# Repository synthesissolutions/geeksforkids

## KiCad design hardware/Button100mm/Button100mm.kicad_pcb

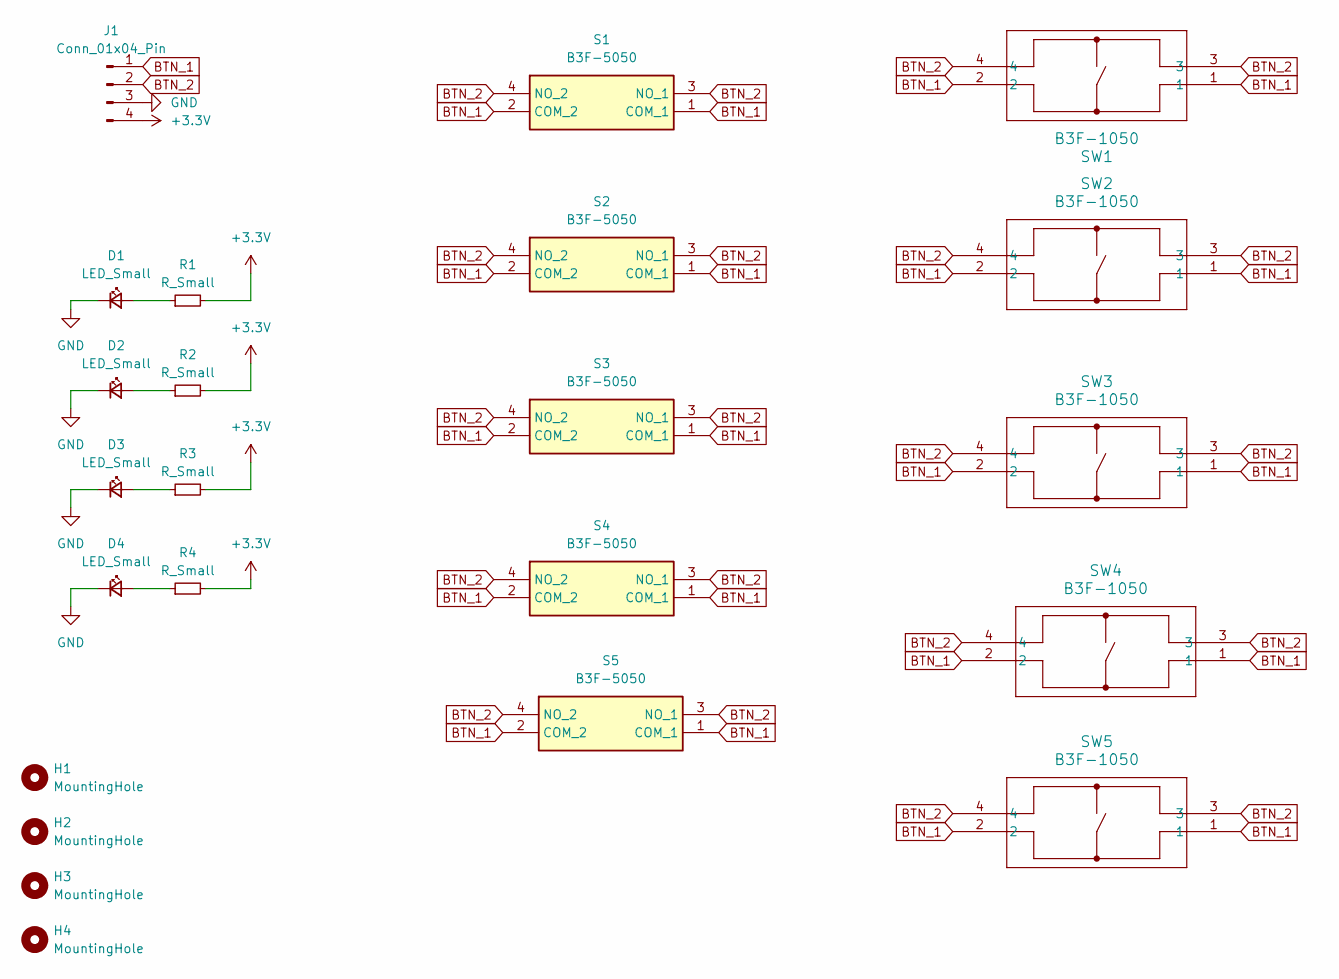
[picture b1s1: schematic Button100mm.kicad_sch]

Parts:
D1, D2, D3, D4: LED_Small; LED_0805_2012Metric
H1, H2, H3, H4: MountingHole; MountingHole_2.7mm_M2.5
J1: Conn_01x04_Pin; JST_XH_B4B-XH-A_1x04_P2.50mm_Vertical
R1, R2, R3, R4: R_Small; R_0805_2012Metric
S1, S2, S3, S4, S5: B3F-5050; B3F-4055; Mouser Part Number 653-B3F-5050
SW1, SW2, SW3, SW4, SW5: B3F-1050; SW_B3F-1050_OMR

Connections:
+3.3V: J1.4, R1.2, R2.2, R3.2, R4.2
BTN_1: J1.1, S1.1 (COM_1), S1.2 (COM_2), S2.1 (COM_1), S2.2 (COM_2), S3.1 (COM_1), S3.2 (COM_2), S4.1 (COM_1), S4.2 (COM_2), S5.1 (COM_1), S5.2 (COM_2), SW1.1, SW1.2, SW2.1, SW2.2, SW3.1, SW3.2, SW4.1, SW4.2, SW5.1, SW5.2
BTN_2: J1.2, S1.3 (NO_1), S1.4 (NO_2), S2.3 (NO_1), S2.4 (NO_2), S3.3 (NO_1), S3.4 (NO_2), S4.3 (NO_1), S4.4 (NO_2), S5.3 (NO_1), S5.4 (NO_2), SW1.3, SW1.4, SW2.3, SW2.4, SW3.3, SW3.4, SW4.3, SW4.4, SW5.3, SW5.4
GND: D1.1 (K), D2.1 (K), D3.1 (K), D4.1 (K), J1.3
unnamed: D1.2 (A), R1.1
unnamed: D2.2 (A), R2.1
unnamed: D3.2 (A), R3.1
unnamed: D4.2 (A), R4.1

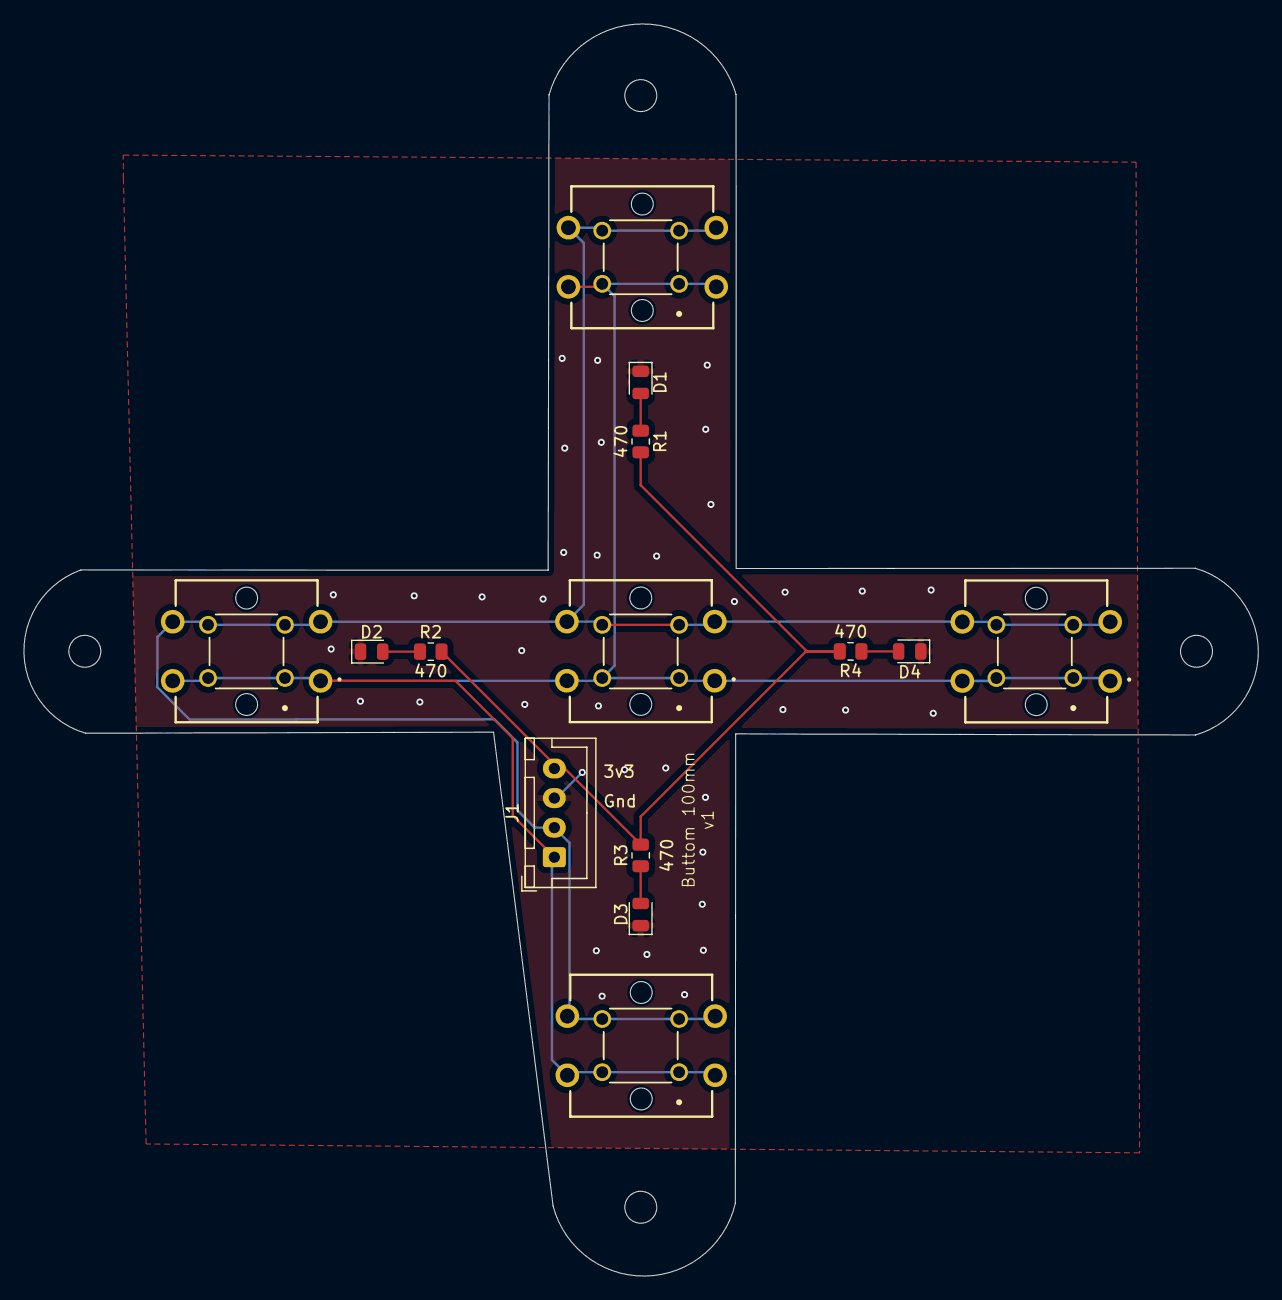
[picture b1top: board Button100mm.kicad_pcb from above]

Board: 2 copper layers, 104.4 x 105.9 mm, 23 parts (0 on the bottom side), 8 nets.

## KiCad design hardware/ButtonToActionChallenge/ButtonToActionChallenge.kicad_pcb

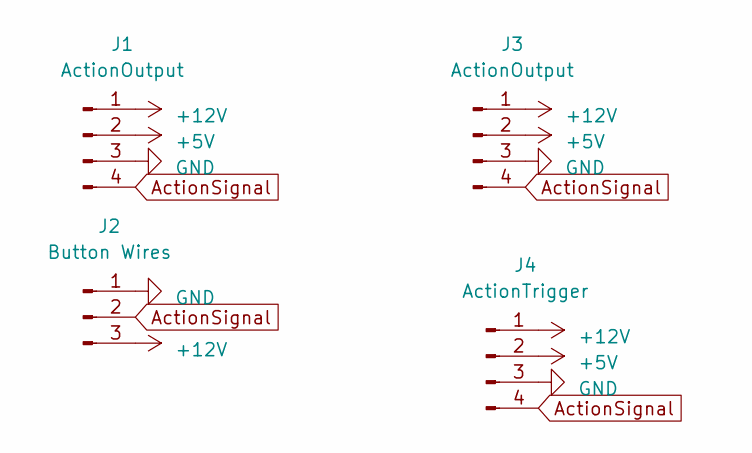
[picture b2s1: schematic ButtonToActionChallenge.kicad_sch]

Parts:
J1: ActionOutput; JST_PH_B4B-PH-K_1x04_P2.00mm_Vertical
J2: Button Wires; JST_XH_B3B-XH-A_1x03_P2.50mm_Vertical
J3: ActionOutput; JST_XH_B4B-XH-A_1x04_P2.50mm_Vertical
J4: ActionTrigger; JST_PH_B4B-PH-K_1x04_P2.00mm_Vertical

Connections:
+5V: J1.2, J3.2, J4.2
+12V: J1.1, J2.3, J3.1, J4.1
ActionSignal: J1.4, J2.2, J3.4, J4.4
GND: J1.3, J2.1, J3.3, J4.3

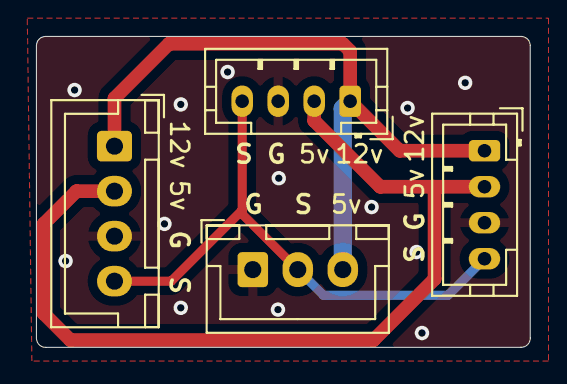
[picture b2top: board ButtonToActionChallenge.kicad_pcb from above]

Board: 2 copper layers, 27.4 x 17.3 mm, 4 parts (0 on the bottom side), 4 nets.

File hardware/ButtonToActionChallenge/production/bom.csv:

Designator,Footprint,Quantity,Value,LCSC Part #
J1,JST_PH_B4B-PH-K_1x04_P2.00mm_Vertical,1,ActionOutput,
J2,JST_XH_B3B-XH-A_1x03_P2.50mm_Vertical,1,Button Wires,
J3,JST_XH_B4B-XH-A_1x04_P2.50mm_Vertical,1,ActionOutput,
J4,JST_PH_B4B-PH-K_1x04_P2.00mm_Vertical,1,ActionTrigger,

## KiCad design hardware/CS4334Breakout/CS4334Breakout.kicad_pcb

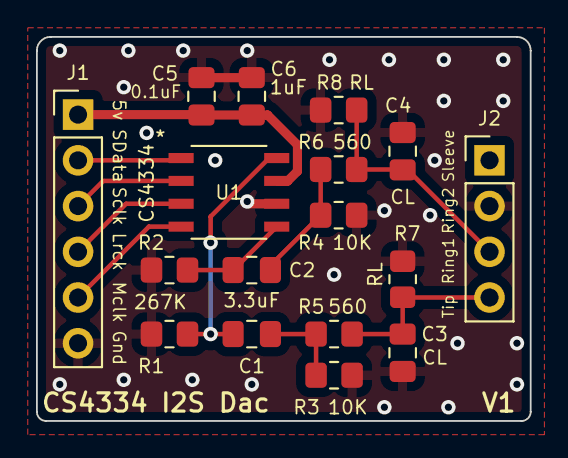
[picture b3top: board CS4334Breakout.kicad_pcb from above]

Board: 2 copper layers, 27.4 x 21.3 mm, 17 parts (0 on the bottom side), 12 nets.

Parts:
C1, C2: 3.3uF; C_0805_2012Metric_Pad1.18x1.45mm_HandSolder
C3, C4: CL; C_0805_2012Metric_Pad1.18x1.45mm_HandSolder
C5: 0.1uF; C_0805_2012Metric_Pad1.18x1.45mm_HandSolder
C6: 1uF; C_0805_2012Metric_Pad1.18x1.45mm_HandSolder
J1: I2S and Power Header; PinHeader_1x06_P2.54mm_Vertical
J2: HeadphoneOutput; PinHeader_1x04_P2.54mm_Vertical
R1, R2: 267K; R_0805_2012Metric_Pad1.20x1.40mm_HandSolder
R3, R4: 10K; R_0805_2012Metric_Pad1.20x1.40mm_HandSolder
R5, R6: 560; R_0805_2012Metric_Pad1.20x1.40mm_HandSolder
R7, R8: RL; R_0805_2012Metric_Pad1.20x1.40mm_HandSolder
U1: CS4334; CS4334-KSZR

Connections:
+5V: C5.1, C6.1, J1.1, U1.7 (VA)
AOUTL: C1.1, R1.1, U1.8 (AOUTL)
AOUTR: C2.1, R2.1, U1.5 (AOUTR)
GND: C3.2, C4.2, C5.2, C6.2, J1.6, J2.2, R1.2, R2.2, R3.2, R4.2, R7.2, R8.2, U1.6 (AGND)
LEFTOUT: C3.1, J2.4, R5.2, R7.1
LRCK: J1.4, U1.3 (LRCK)
MCLK: J1.5, U1.4 (MCLK)
unnamed: C1.2, R3.1, R5.1
unnamed: C2.2, R4.1, R6.1
RIGHTOUT: C4.1, J2.3, R6.2, R8.1
SCLK: J1.3, U1.2 (DEM/SCLK)
SDATA: J1.2, U1.1 (SDATA)

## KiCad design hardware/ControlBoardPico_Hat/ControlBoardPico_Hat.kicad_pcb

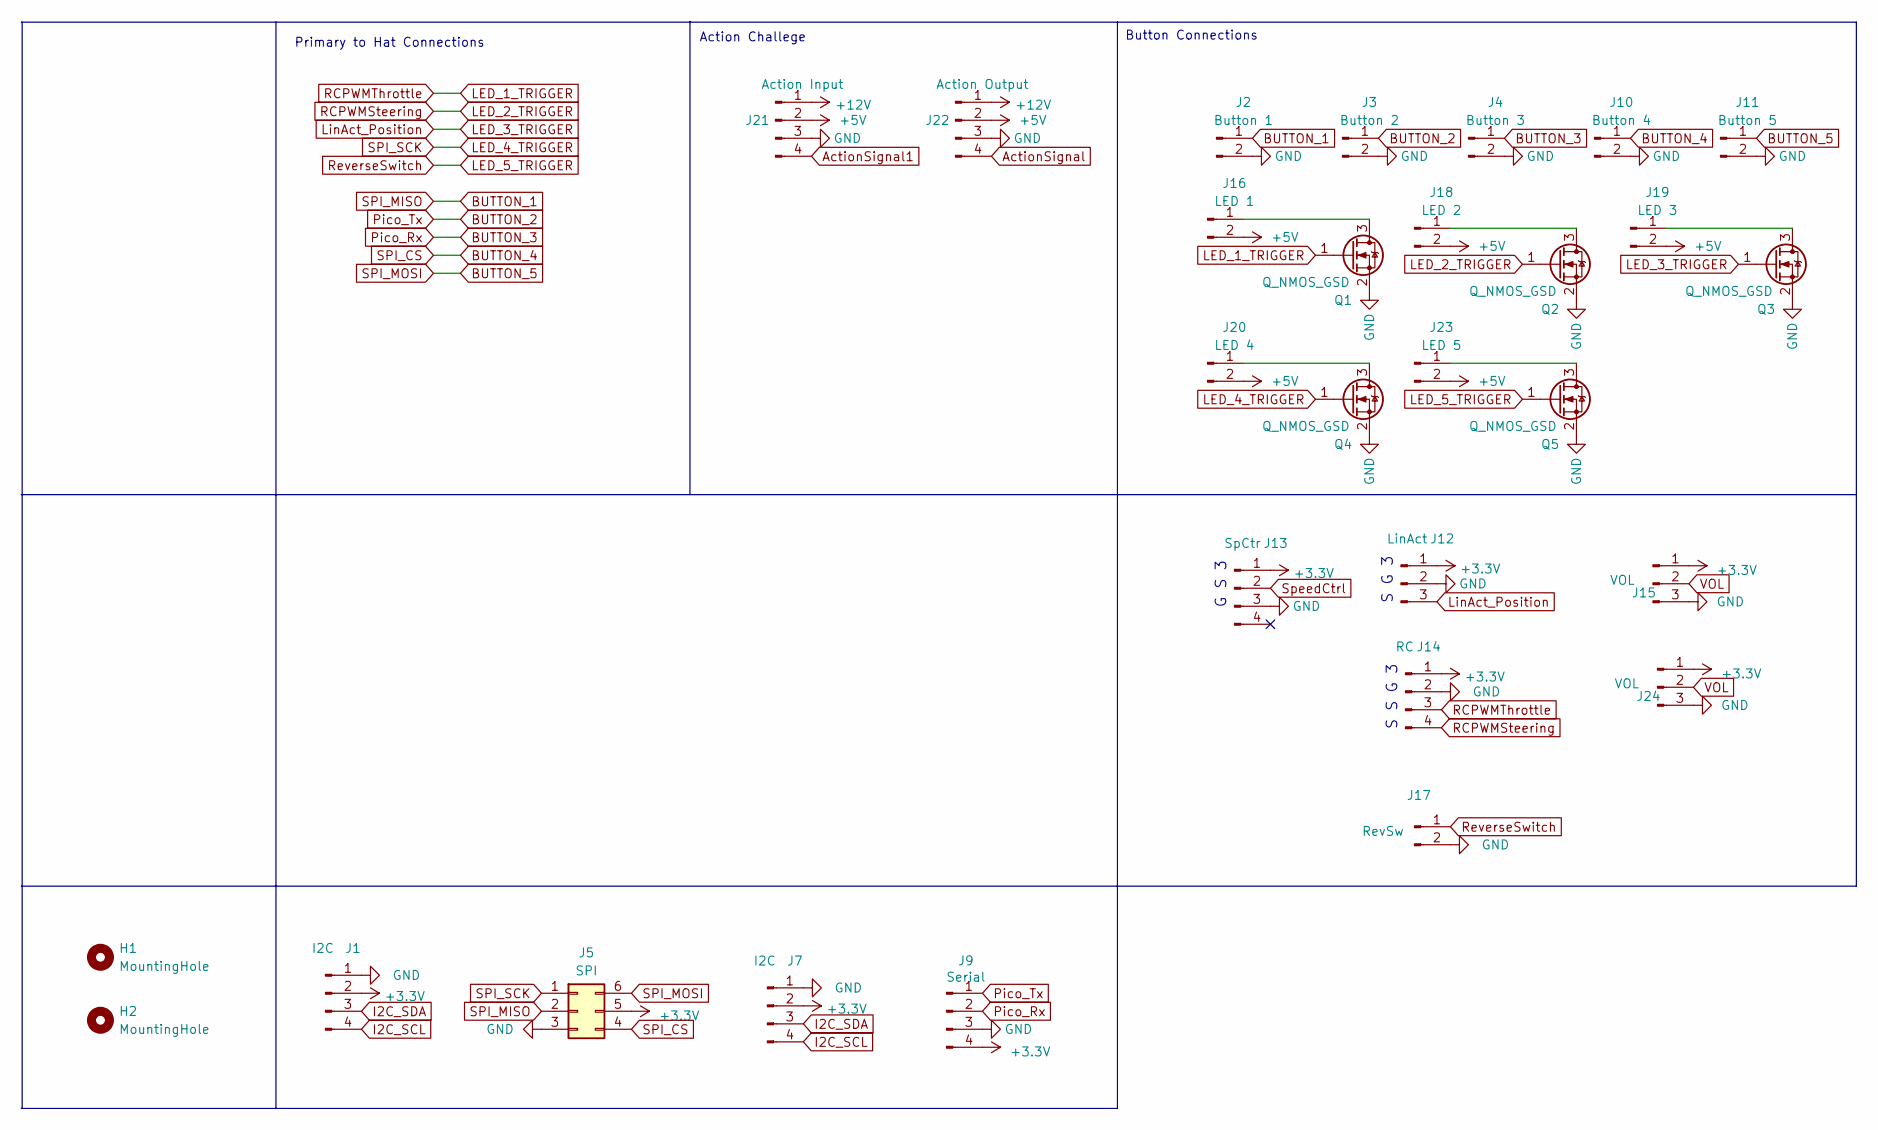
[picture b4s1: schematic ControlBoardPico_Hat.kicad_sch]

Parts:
H1, H2: MountingHole; MountingHole_2.7mm_M2.5
J1: I2C; JST_SH_BM04B-SRSS-TB_1x04-1MP_P1.00mm_Vertical
J2: Button 1; JST_XH_B2B-XH-A_1x02_P2.50mm_Vertical
J3: Button 2; JST_XH_B2B-XH-A_1x02_P2.50mm_Vertical
J4: Button 3; JST_XH_B2B-XH-A_1x02_P2.50mm_Vertical
J5: SPI; PinHeader_2x03_P2.54mm_Vertical
J7: I2C; PinHeader_1x04_P2.54mm_Vertical
J9: Serial; PinHeader_1x04_P2.54mm_Vertical
J10: Button 4; JST_XH_B2B-XH-A_1x02_P2.50mm_Vertical
J11: Button 5; JST_XH_B2B-XH-A_1x02_P2.50mm_Vertical
J12: LinAct; PinSocket_1x03_P2.54mm_Vertical
J13: SpCtr; PinSocket_1x04_P2.00mm_Vertical
J14: RC; PinSocket_1x04_P2.54mm_Vertical
J15: VOL; PinSocket_1x03_P2.00mm_Vertical
J16: LED 1; JST_XH_B2B-XH-A_1x02_P2.50mm_Vertical
J17: RevSw; PinSocket_1x02_P2.54mm_Vertical
J18: LED 2; JST_XH_B2B-XH-A_1x02_P2.50mm_Vertical
J19: LED 3; JST_XH_B2B-XH-A_1x02_P2.50mm_Vertical
J20: LED 4; JST_XH_B2B-XH-A_1x02_P2.50mm_Vertical
J21: Action Input; PinSocket_1x04_P2.54mm_Vertical
J22: Action Output; PinSocket_1x04_P2.54mm_Vertical
J23: LED 5; JST_XH_B2B-XH-A_1x02_P2.50mm_Vertical
J24: VOL; JST_XH_B3B-XH-A_1x03_P2.50mm_Vertical
Q1, Q2, Q3, Q4, Q5: Q_NMOS_GSD; SOT-23

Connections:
+3.3V: J1.2, J5.5, J7.2, J9.4, J12.1, J13.1, J14.1, J15.1, J24.1
+5V: J16.2, J18.2, J19.2, J20.2, J21.2, J22.2, J23.2
+12V: J21.1, J22.1
ActionSignal: J22.4
ActionSignal1: J21.4
BUTTON_1: J2.1, J5.2
BUTTON_2: J3.1, J9.1
BUTTON_3: J4.1, J9.2
BUTTON_4: J5.4, J10.1
BUTTON_5: J5.6, J11.1
GND: J1.1, J2.2, J3.2, J4.2, J5.3, J7.1, J9.3, J10.2, J11.2, J12.2, J13.3, J14.2, J15.3, J17.2, J21.3, J22.3, J24.3, Q1.2 (S), Q2.2 (S), Q3.2 (S), Q4.2 (S), Q5.2 (S)
I2C_SCL: J1.4, J7.4
I2C_SDA: J1.3, J7.3
LED_1_TRIGGER: J14.3, Q1.1 (G)
LED_2_TRIGGER: J14.4, Q2.1 (G)
LED_3_TRIGGER: J12.3, Q3.1 (G)
LED_4_TRIGGER: J5.1, Q4.1 (G)
LED_5_TRIGGER: J17.1, Q5.1 (G)
unnamed: J16.1, Q1.3 (D)
unnamed: J18.1, Q2.3 (D)
unnamed: J19.1, Q3.3 (D)
unnamed: J20.1, Q4.3 (D)
unnamed: J23.1, Q5.3 (D)
SpeedCtrl: J13.2
VOL: J15.2, J24.2

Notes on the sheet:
G S 3
S S G 3
Button Connections
Primary to Hat Connections
Action Challege
S G 3

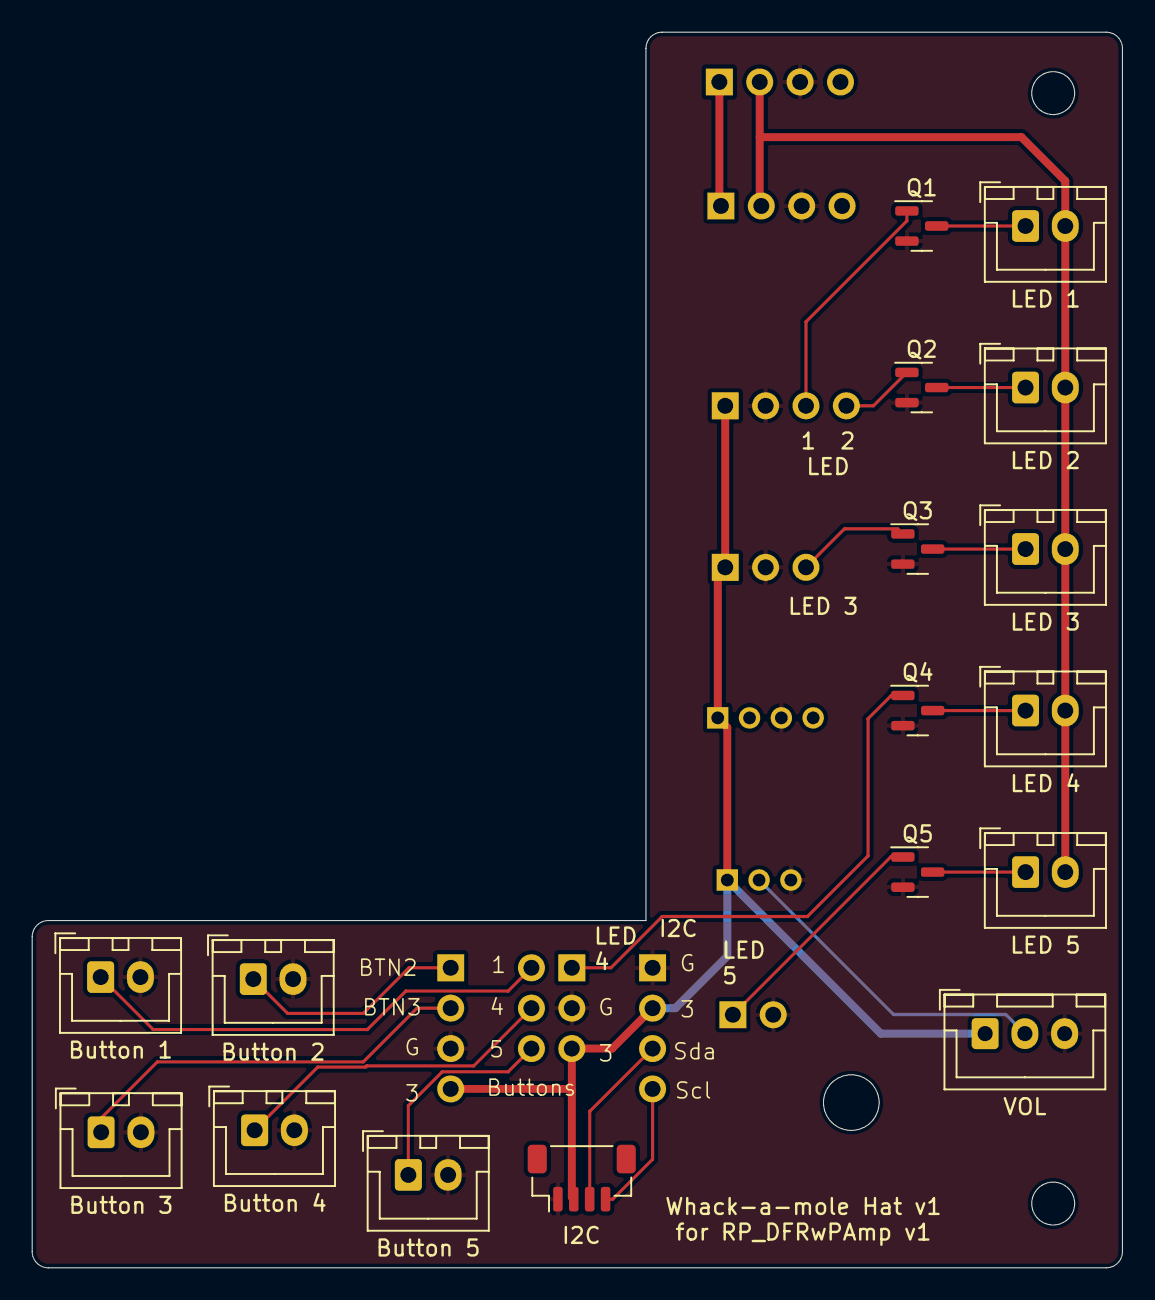
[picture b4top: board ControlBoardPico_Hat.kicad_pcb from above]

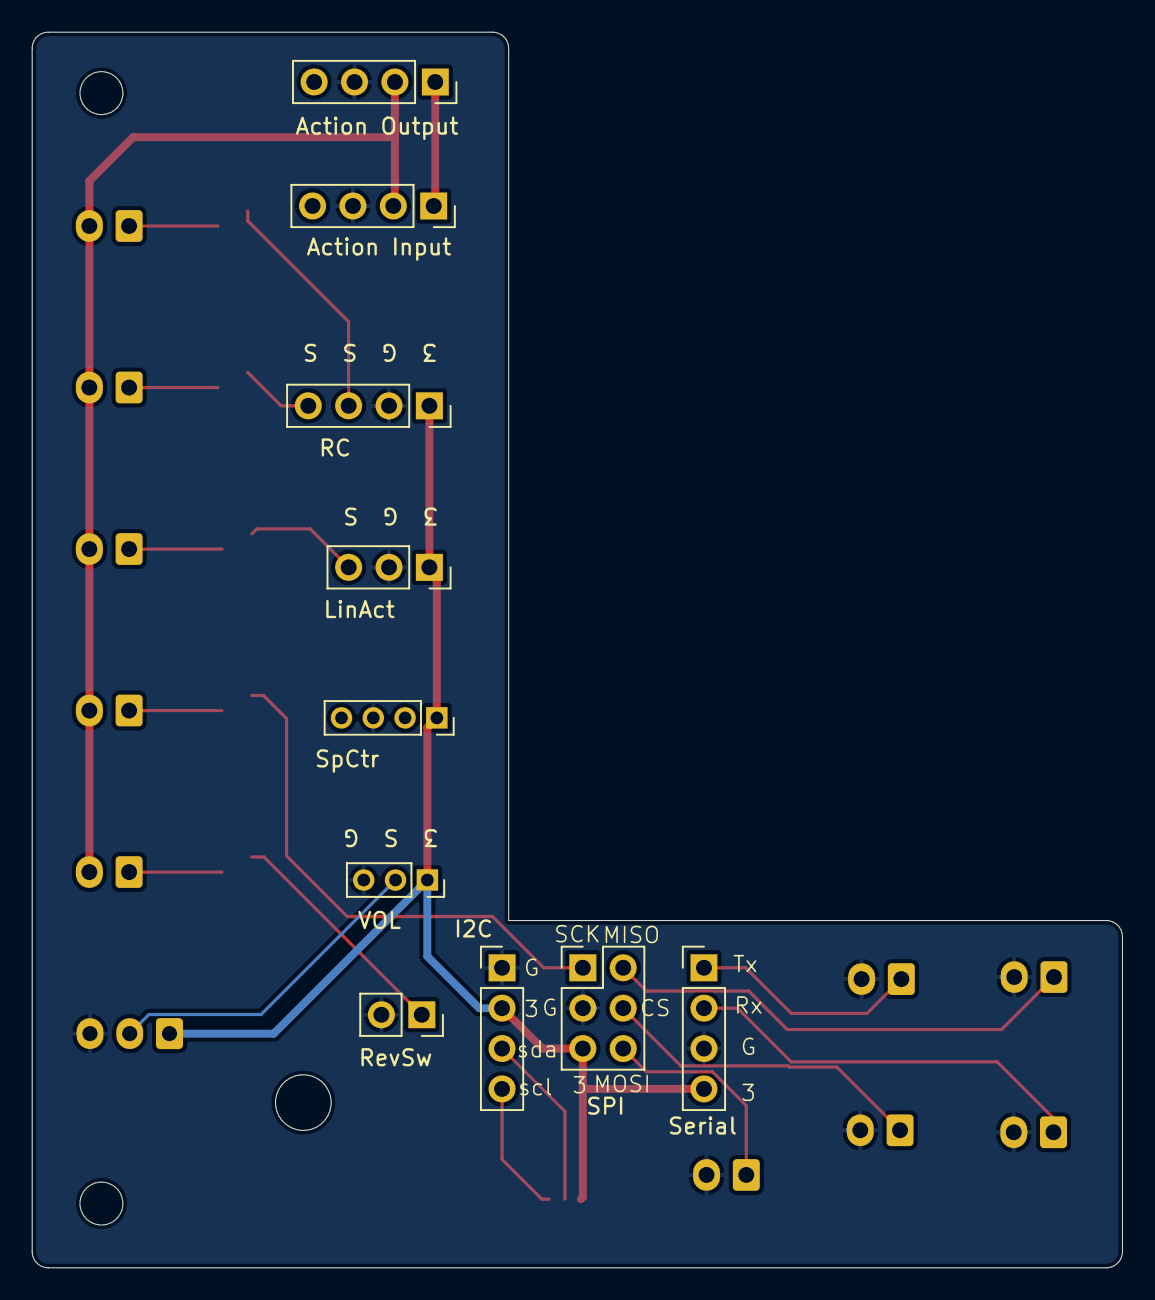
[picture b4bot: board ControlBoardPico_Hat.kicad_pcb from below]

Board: 2 copper layers, 68.6 x 77.7 mm, 29 parts (10 on the bottom side), 22 nets.

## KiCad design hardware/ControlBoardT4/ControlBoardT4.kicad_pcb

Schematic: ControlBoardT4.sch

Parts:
BT1: 5v+ -; PinHeader_1x02_P2.54mm_Vertical
J1: RC; PinHeader_1x04_P2.54mm_Vertical
J2: LinAct; PinHeader_1x03_P2.54mm_Vertical
J3: sPOT; PinHeader_1x03_P2.54mm_Vertical
J4: Other 1 & 2; PinHeader_2x03_P2.54mm_Vertical
J5: [Other Connections 1-6]; PinHeader_2x03_P2.54mm_Vertical
J6: Other 5 & 6; PinHeader_2x03_P2.54mm_Vertical
J7: 8P8C; RJ45_Amphenol_54602-x08_Horizontal
J8: Motor Driver; PinHeader_2x05_P2.54mm_Vertical
J9: FXSound; FXSound_2x11_P2.54mm
J10: BT Switch; PinHeader_1x02_P2.54mm_Vertical
J11: AudioJack4; Jack_3.5mm_PJ320A_Horizontal
J12: BT; PinHeader_1x06_P2.54mm_Vertical
JP1: Serial Sound; SolderJumper-2_P1.3mm_Open_TrianglePad1.0x1.5mm
JP2, JP3: Digial Sound; SolderJumper-2_P1.3mm_Open_TrianglePad1.0x1.5mm
R1: R; R_Axial_DIN0207_L6.3mm_D2.5mm_P7.62mm_Horizontal
U1: Teensy4.0_NoMid; Teensy40_NoMid
U2: NA555; DIP-8_W7.62mm

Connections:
+3V3: J1.1, J2.1, J3.1, J4.1, J4.2, J5.1, J5.2, J6.1, J6.2, J7.7, U1.26
+5V: BT1.1 (+), J7.2, J8.1, J8.2, J9.2, R1.2, U1.28, U2.4 (R), U2.7 (DIS), U2.8 (VCC)
GND: BT1.2 (-), J1.2, J2.2, J3.2, J4.3, J4.4, J5.3, J5.4, J6.3, J6.4, J7.1, J8.3, J8.4, J9.4, J10.2, J12.3, JP1.2, U1.1, U2.1 (GND), U2.5 (CV), U2.6 (THR)
unnamed: J1.3, U1.12
unnamed: J1.4, U1.13
unnamed: J2.3, U1.21
unnamed: J3.3, U1.20
unnamed: J4.5, U1.19
unnamed: J4.6, U1.18
unnamed: J5.5, U1.11
unnamed: J5.6, U1.10
unnamed: J6.5, U1.15
unnamed: J6.6, U1.14
unnamed: J7.3, JP2.1, U1.25
unnamed: J7.4, JP3.1, U1.24
unnamed: J7.5, U1.23
unnamed: J7.6, U1.22
unnamed: J8.5, U1.6
unnamed: J8.6, U1.9
unnamed: J8.7, U1.5
unnamed: J8.8, U1.8
unnamed: J8.9, U1.4
unnamed: J8.10, U1.7
unnamed: J9.5, JP2.2
unnamed: J9.7, JP3.2
unnamed: J9.8, U1.2
unnamed: J9.10, U1.3
unnamed: J9.12, JP1.1
unnamed: J10.1, R1.1, U2.2 (TR)
unnamed: J9.18, J11.R1
unnamed: J9.22, J11.S
unnamed: J9.20, J11.T
unnamed: J12.2, U2.3 (Q)
unnamed: J12.4, U1.17
unnamed: J12.5, U1.16

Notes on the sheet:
3 Y X 2 1 5 G
3 G S S
5 G S S S
3 G S
T R U
R L G
E 5 G T R S

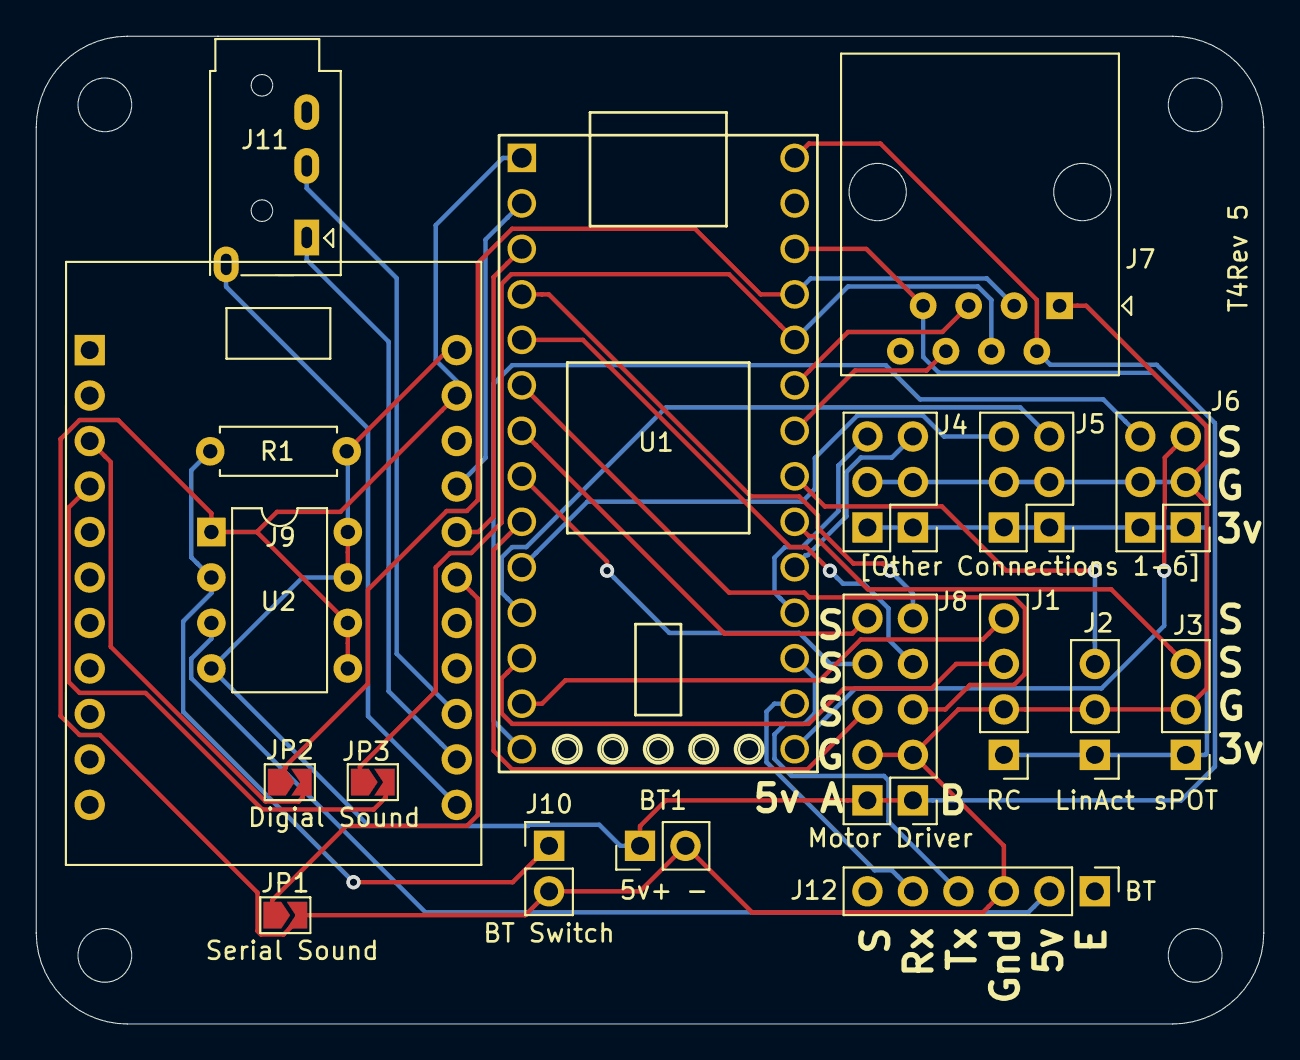
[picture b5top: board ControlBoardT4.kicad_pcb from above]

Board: 2 copper layers, 68.6 x 55.2 mm, 19 parts (0 on the bottom side), 35 nets.

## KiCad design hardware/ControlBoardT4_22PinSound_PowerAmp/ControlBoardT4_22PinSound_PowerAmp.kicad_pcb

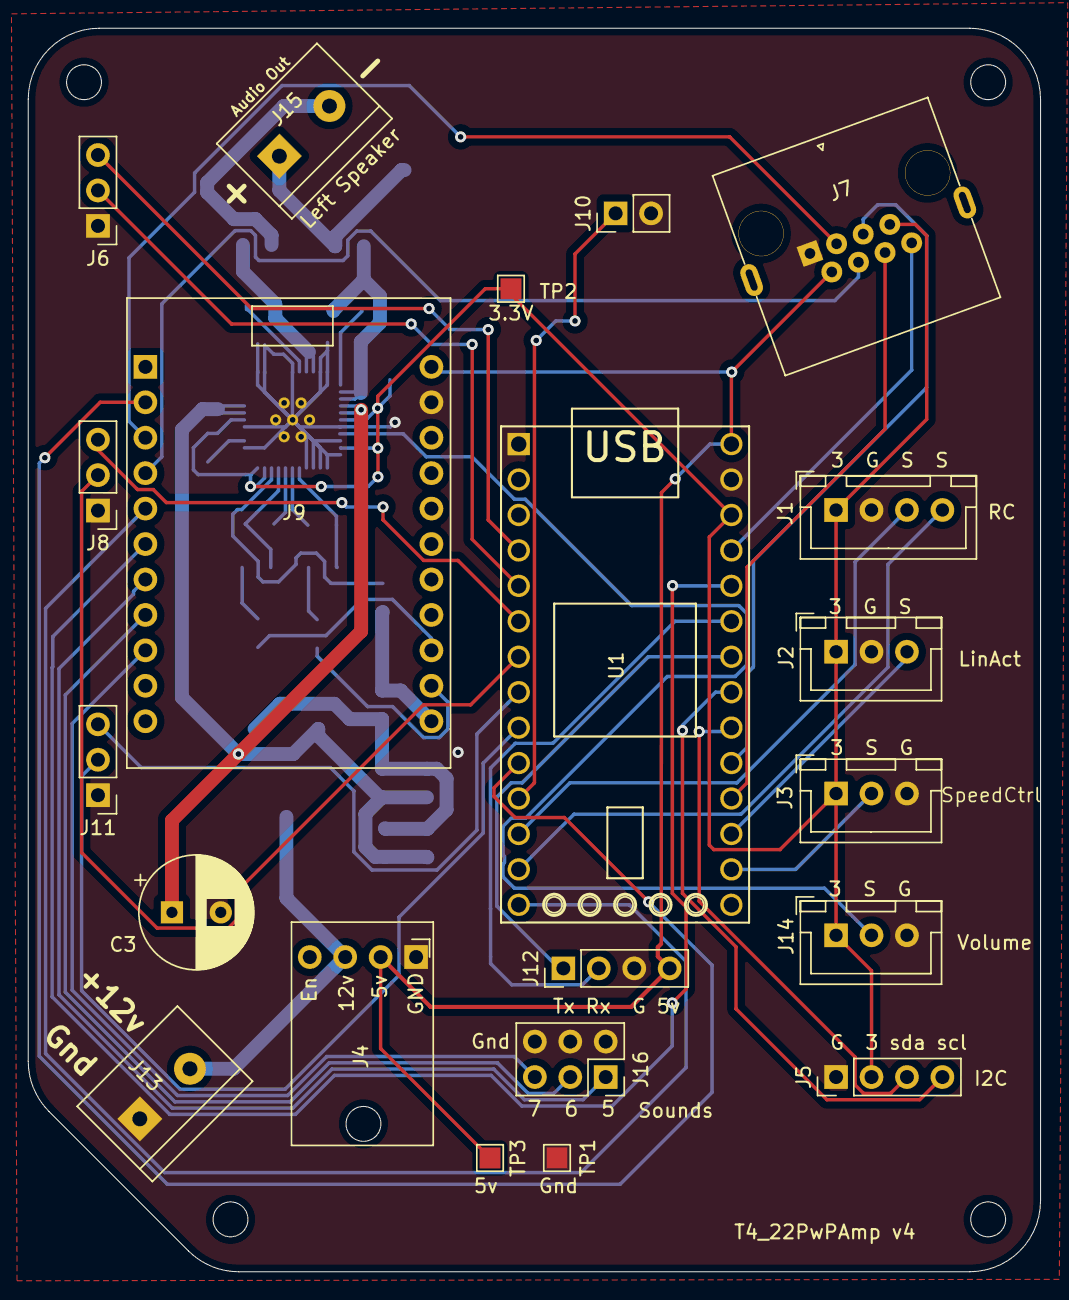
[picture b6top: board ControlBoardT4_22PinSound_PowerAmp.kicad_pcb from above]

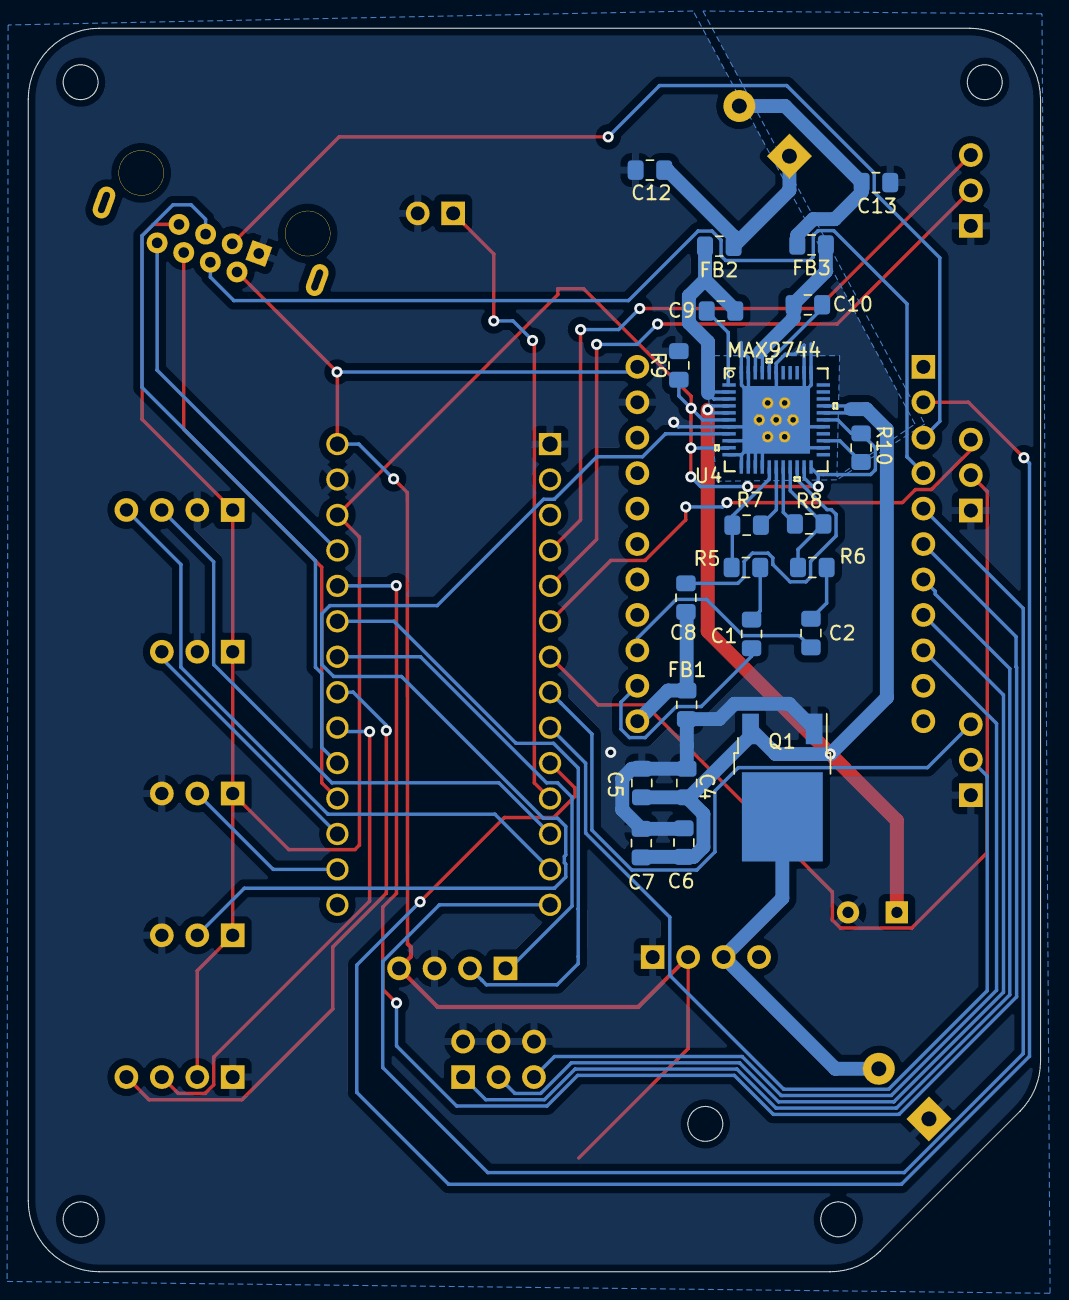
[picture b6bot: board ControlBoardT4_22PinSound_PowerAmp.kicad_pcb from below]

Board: 2 copper layers, 72.6 x 89.1 mm, 43 parts (22 on the bottom side), 49 nets.

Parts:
C1, C2: 0.47µF; C_0805_2012Metric_Pad1.15x1.40mm_HandSolder
C3: 470µF; CP_Radial_D8.0mm_P3.50mm
C4, C5: 10µF; C_0805_2012Metric_Pad1.15x1.40mm_HandSolder
C6, C7, C9, C10: 0.1µF; C_0805_2012Metric_Pad1.15x1.40mm_HandSolder
C8: 2.2µF; C_0805_2012Metric_Pad1.15x1.40mm_HandSolder
C12, C13: 470pF; C_0805_2012Metric_Pad1.15x1.40mm_HandSolder
FB1, FB2, FB3: MPZ2012S221AT00; L_0805_2012Metric_Pad1.15x1.40mm_HandSolder
J1: RC; JST_XH_B4B-XH-A_1x04_P2.54mm_Vertical
J2: LinAct; JST_XH_B3B-XH-A_1x03_P2.54mm_Vertical
J3: SpeedCtrl; JST_XH_B3B-XH-A_1x03_P2.54mm_Vertical
J4: Power Input; AdaFruit_MPM3610
J5: I2C; PinHeader_1x04_P2.54mm_Vertical
J6: Left_M1; PinHeader_1x03_P2.54mm_Vertical
J7: 8P8C; RJ45_x08_Tab_Up
J8: Right_M2; PinHeader_1x03_P2.54mm_Vertical
J9: 22Pin_FXSound; FXSound_2x11_P2.54mm_Short
J10: Conn_01x02_Male; PinHeader_1x02_P2.54mm_Vertical
J11: LinAct_M3; PinHeader_1x03_P2.54mm_Vertical
J12: Conn_01x04_Male; PinHeader_1x04_P2.54mm_Vertical
J13: Main Power; TerminalBlock_bornier-2_P5.08mm
J14: Volume; JST_XH_B3B-XH-A_1x03_P2.54mm_Vertical
J15: Left Speaker; TerminalBlock_bornier-2_P5.08mm
J16: Additional Sound Header; PinSocket_2x03_P2.54mm_Vertical
Q1: AOD417; TO-252-2pin3D
R5, R6, R7, R8: 20K; R_0805_2012Metric_Pad1.15x1.40mm_HandSolder
R9, R10: 10K; R_0805_2012Metric_Pad1.15x1.40mm_HandSolder
TP1: Gnd; TestPoint_Pad_1.5x1.5mm
TP2: 3.3V; TestPoint_Pad_1.5x1.5mm
TP3: 5v; TestPoint_Pad_1.5x1.5mm
U1: Teensy4.0_NoMid; Teensy40_NoMid
U4: MAX9744; max9744eth&plus_Mod

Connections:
+3V3: J1.1, J2.1, J3.1, J5.2, J7.7, J14.1, R9.1, R10.2, TP2.1, U1.26 (3.3V_max250mA), U4.6 (VDD), U4.10 (VDD), U4.21 (VDD), U4.22 (SHDN), U4.28 (VDD)
+5V: J4.2, J7.2, J9.2, J12.4, TP3.1, U1.28 (Vin)
+12V: J4.3, J13.2, Q1.3 (D)
ActiveSW: J7.8, U1.25 (23_A9_CRX1_MCLK1_PWM)
GND: C3.2, C4.1, C5.1, C6.1, C7.1, C12.1, C13.2, FB1.2, J1.2, J2.2, J3.3, J4.1, J5.1, J6.1, J7.1, J8.1, J9.4, J10.2, J11.1, J12.3, J13.1, J14.3, J16.2, J16.4, J16.6, Q1.1 (G), R9.2, TP1.1, U1.1 (GND), U1.27 (GND), U4.7 (GND), U4.9 (SCLK), U4.11 (GND), U4.12 (GND), U4.13 (ADDR1), U4.14 (ADDR2), U4.15 (GND), U4.24 (MUTE), U4.27 (GND), U4.34 (PGND), U4.35 (PGND), U4.39 (PGND), U4.43 (PGND), U4.44 (PGND), U4.45 (THERM)
GNDA: C8.2, FB1.1, J9.22
I2C_SCL: J5.4, U1.21 (19_A5_SCL0_PWM)
I2C_SDA: J5.3, U1.20 (18_A4_SDA0_PWM)
LeftIN: C1.2, J9.20
Left_DIR: J6.2, U1.5 (3_LRCLK2_PWM)
Left_PWM: J6.3, U1.4 (2_OUT2_PWM)
LinAct_DIR: J11.2, U1.9 (7_RX2_OUT1A_PWM)
LinAct_PWM: J11.3, U1.8 (6_OUT1D_PWM)
LinAct_Position: J2.3, U1.17 (15_A1_RX3_S/PDIFIN_PWM)
unnamed: C1.1, R5.2
unnamed: C2.1, R6.2
unnamed: C3.1, C4.2, C5.2, C6.2, C7.2, Q1.2 (S), U4.4 (PVDD), U4.5 (PVDD), U4.29 (PVDD), U4.30 (PVDD)
unnamed: C8.1, U4.20 (BIAS)
unnamed: C9.1, FB2.1, U4.2 (OUTL+), U4.3 (OUTL+)
unnamed: C9.2, U4.1 (BOOTL+)
unnamed: C10.1, FB3.1, U4.41 (OUTL-), U4.42 (OUTL-)
unnamed: C10.2, U4.40 (BOOTL-)
unnamed: C12.2, FB2.2, J15.1
unnamed: C13.1, FB3.2, J15.2
unnamed: R5.1, R7.2, U4.16 (INL)
unnamed: R6.1, R8.2, U4.19 (INR)
unnamed: R7.1, U4.17 (FBL)
unnamed: R8.1, U4.18 (FBR)
unnamed: R10.1, U4.25 (SYNC)
PgSwitch: J10.1, U1.11 (9_OUT1C_PWM)
RCPWMSteering: J1.4, U1.13 (11_MOSI_CTX1_PWM)
RCPWMThrottle: J1.3, U1.12 (10_CS_MQSR_PWM)
RightIN: C2.2, J9.18
Right_DIR: J8.2, U1.7 (5_IN2_PWM)
Right_PWM: J8.3, U1.6 (4_BCLK2_PWM)
RxA7: J12.2, U1.23 (21_A7_RX5_BCLK1)
Sound0: J9.3, U1.10 (8_TX2_IN1_PWM)
Sound1: J7.3, J9.5
Sound2: J7.4, J9.7
Sound3: J9.9, U1.14 (12_MISO_MQSL_PWM)
Sound4: J9.11, U1.24 (22_A8_CTX1_PWM)
Sound5: J9.13, J16.1
Sound6: J9.15, J16.3
Sound7: J9.17, J16.5
SpeedCtrl: J3.2, U1.16 (14_A0_TX3_S/PDIFOUT_PWM)
Steering: J7.5, U1.19 (17_A3_SDA1_PWM)
Throttle: J7.6, U1.18 (16_A2_SCL1_PWM)
TxA6: J12.1, U1.22 (20_A6_TX5_LRCLK1)
VOL: J14.2, U4.8 (SDA/VOL)
